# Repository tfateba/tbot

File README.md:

# tbot
tbot is a self balancing robot made to have fun while learning concepts of several disciplines.

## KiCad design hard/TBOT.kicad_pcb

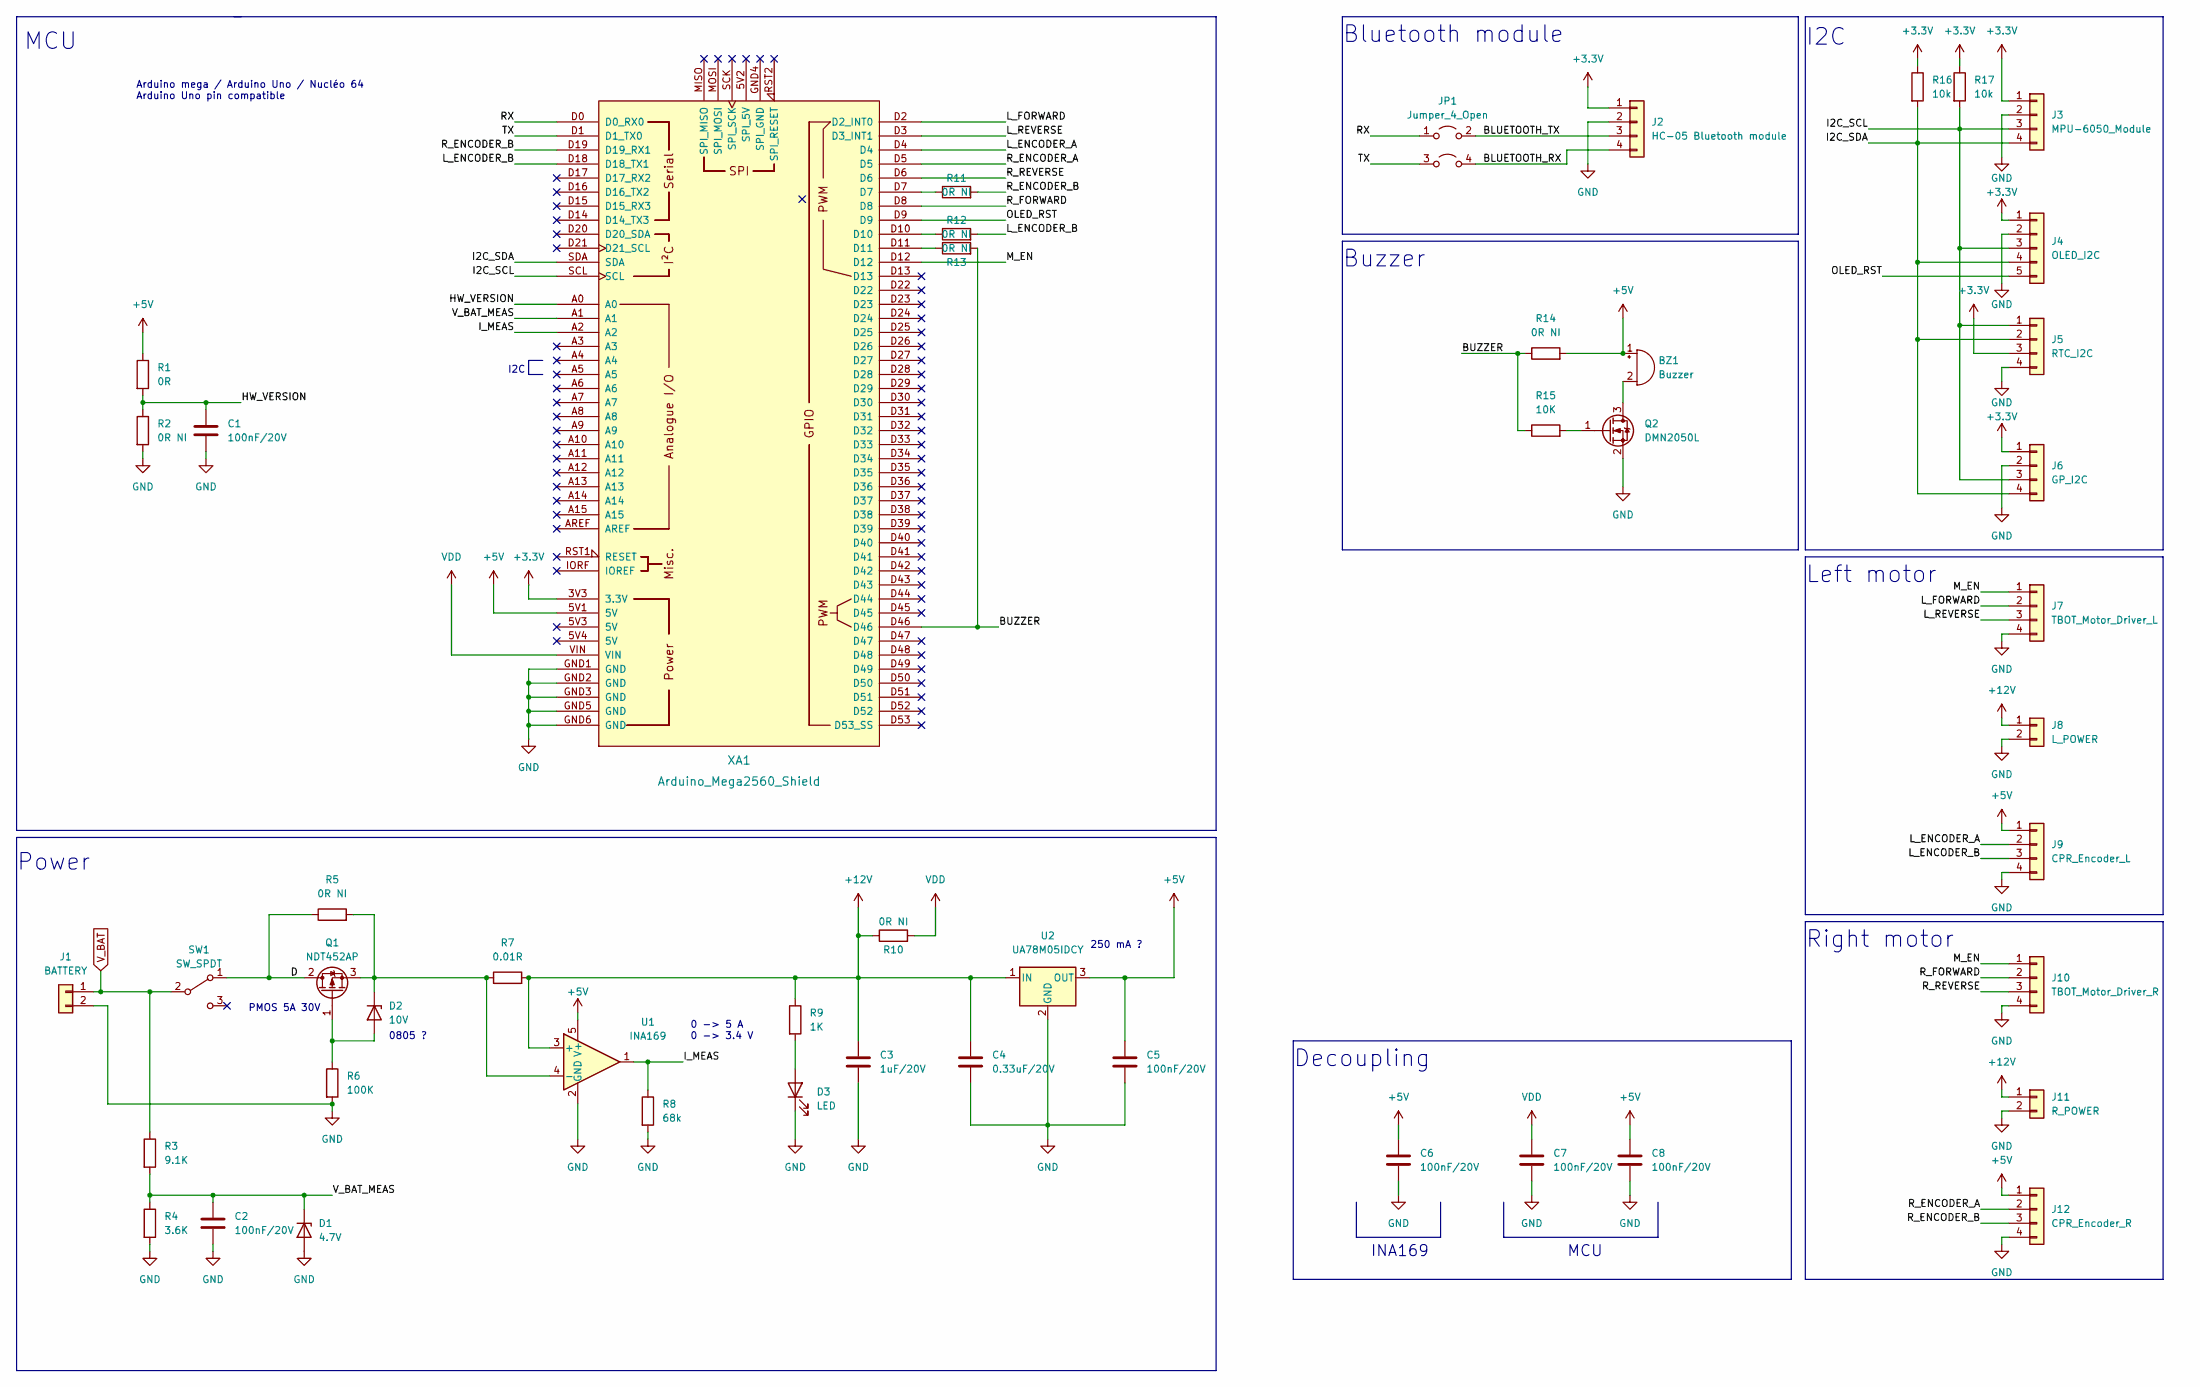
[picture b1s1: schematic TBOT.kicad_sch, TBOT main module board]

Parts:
BZ1: Buzzer; Buzzer_12x9.5RM7.6
C1, C2, C5, C6, C7, C8: 100nF/20V; C_0805_2012Metric
C3: 1uF/20V; C_0805_2012Metric
C4: 0.33uF/20V; C_0805_2012Metric
D1: 4.7V; D_SOD-323
D2: 10V; D_SOD-323
D3: LED; LED_0805_2012Metric
J1: BATTERY; TerminalBlock_Phoenix_MKDS-1,5-2-5.08_1x02_P5.08mm_Horizont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
J2: HC-05 Bluetooth module; PinSocket_1x04_P2.54mm_Horizontal
J3: MPU-6050_Module
J4: OLED_I2C; PinSocket_1x05_P2.54mm_Vertical
J5: RTC_I2C; PinSocket_1x04_P2.54mm_Vertical
J6: GP_I2C; PinSocket_1x04_P2.54mm_Vertical
J7: TBOT_Motor_Driver_L; PinHeader_1x04_P2.54mm_Vertical
J8: L_POWER; TerminalBlock_Phoenix_MKDS-1,5-2-5.08_1x02_P5.08mm_Horizont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
J9: CPR_Encoder_L; TerminalBlock_Phoenix_MPT-0,5-4-2.54_1x04_P2.54mm_Horizontal
J10: TBOT_Motor_Driver_R; PinHeader_1x04_P2.54mm_Vertical
J11: R_POWER; TerminalBlock_Phoenix_MKDS-1,5-2-5.08_1x02_P5.08mm_Horizont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
J12: CPR_Encoder_R; TerminalBlock_Phoenix_MPT-0,5-4-2.54_1x04_P2.54mm_Horizontal
JP1: Jumper_4_Open; PinHeader_2x02_P2.54mm_Vertical
Q1: NDT452AP; SOT-223-3_TabPin2
Q2: DMN2050L; SOT-23
R1: 0R; R_0805_2012Metric
R2, R5, R10, R11, R12, R13, R14: 0R NI; R_0805_2012Metric
R3: 9.1K; R_0805_2012Metric
R4: 3.6K; R_0805_2012Metric
R6: 100K; R_0805_2012Metric
R7: 0.01R; R_0805_2012Metric
R8: 68k; R_0805_2012Metric
R9: 1K; R_0805_2012Metric
R15: 10K; R_0805_2012Metric
R16, R17: 10k; R_0805_2012Metric
SW1: SW_SPDT; 5638A
U1: INA169; SOT-23-5
U2: UA78M05IDCY; SOT-223
XA1: Arduino_Mega2560_Shield

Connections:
+3.3V: J2.1, J3.1, J4.1, J5.3, J6.1, R16.1, R17.1, XA1.3V3 (3.3V)
+5V: BZ1.1 (-), C5.1, C6.1, C8.1, J9.1, J12.1, R1.1, R14.2, U1.5 (V+), U2.3 (OUT), XA1.5V1 (5V)
+12V: C3.1, C4.1, J8.1, J11.1, R7.2, R9.1, R10.1, U1.3 (+), U2.1 (IN)
/BLUETOOTH_RX: J2.4, JP1.4 (D)
/BLUETOOTH_TX: J2.3, JP1.2 (B)
/BUZZER: R13.2, R14.1, R15.1, XA1.D46
/D: Q1.2 (D), R5.1, SW1.1 (A)
/HW_VERSION: C1.1, R1.2, R2.1, XA1.A0
/I2C_SCL: J3.3, J4.3, J5.1, J6.3, R17.2, XA1.SCL
/I2C_SDA: J3.4, J4.4, J5.2, J6.4, R16.2, XA1.SDA
/I_MEAS: R8.1, U1.1, XA1.A2
/L_ENCODER_A: J9.2, XA1.D4
/L_ENCODER_B: J9.3, R12.2, XA1.D18 (D18_TX1)
/L_FORWARD: J7.2, XA1.D2 (D2_INT0)
/L_REVERSE: J7.3, XA1.D3 (D3_INT1)
/M_EN: J7.1, J10.1, XA1.D12
/OLED_RST: J4.5, XA1.D9
/RX: JP1.1 (A), XA1.D0 (D0_RX0)
/R_ENCODER_A: J12.2, XA1.D5
/R_ENCODER_B: J12.3, R11.2, XA1.D19 (D19_RX1)
/R_FORWARD: J10.2, XA1.D8
/R_REVERSE: J10.3, XA1.D6
/TX: JP1.3 (C), XA1.D1 (D1_TX0)
/V_BAT_MEAS: C2.1, D1.1 (K), R3.2, R4.1, XA1.A1
GND: C1.2, C2.2, C3.2, C4.2, C5.2, C6.2, C7.2, C8.2, D1.2 (A), D3.1 (K), J1.2, J2.2, J3.2, J4.2, J5.4, J6.2, J7.4, J8.2, J9.4, J10.4, J11.2, J12.4, Q2.2 (S), R2.2, R4.2, R6.2, R8.2, U1.2 (GND), U2.2 (GND), XA1.GND1 (GND), XA1.GND2 (GND), XA1.GND3 (GND), XA1.GND5 (GND), XA1.GND6 (GND)
unnamed: BZ1.2 (+), Q2.3 (D)
unnamed: D2.1 (K), Q1.3 (S), R5.2, R7.1, U1.4 (-)
unnamed: D2.2 (A), Q1.1 (G), R6.1
unnamed: D3.2 (A), R9.2
unnamed: R11.1, XA1.D7
unnamed: R12.1, XA1.D10
unnamed: R13.1, XA1.D11
unnamed: Q2.1 (G), R15.2
VDD: C7.1, R10.2, XA1.VIN
V_BAT: J1.1, R3.1, SW1.2 (B)

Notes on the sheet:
250 mA ?
INA169
MCU
Right motor
0 -> 5 A 0 -> 3.4 V
Bluetooth module
Decoupling
Arduino mega / Arduino Uno / Nucléo 64 Arduino Uno pin compatible
I2C
Buzzer
0805 ?
I2C
Left motor
Power
PMOS 5A 30V

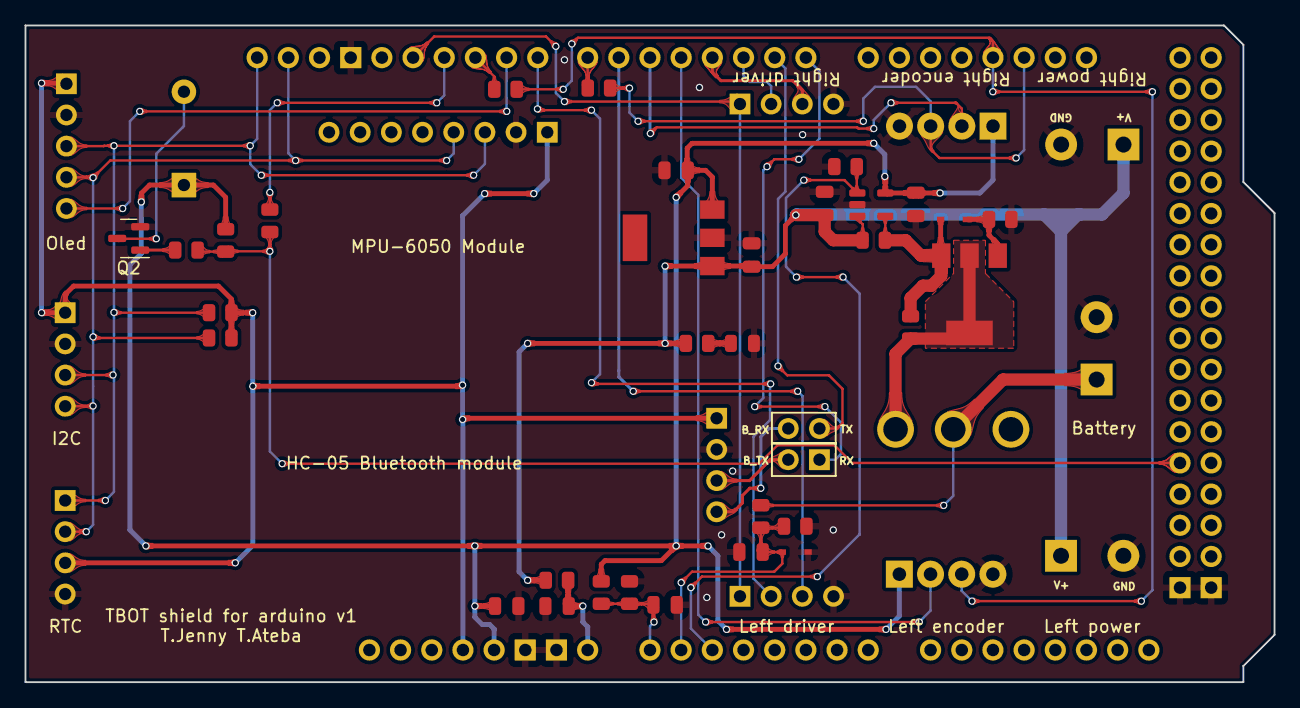
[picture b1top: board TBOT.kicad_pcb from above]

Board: 2 copper layers, 101.8 x 53.5 mm, 48 parts (0 on the bottom side), 35 nets.

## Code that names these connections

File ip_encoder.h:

/**
 *
 * @file    ip_encoder.h
 *
 * @brief   Encoder header file.
 *
 * @author  Theodore Ateba, tf.ateba@gmail.com
 *
 * @date    27 August 2017
 *
 */

#ifndef IP_ENCODER_H
#define IP_ENCODER_H

/* Arduino Interruption */
#define INT2 2      /**< D19 [PD2], BLACK wire motor Right                  */
#define INT3 3      /**< D18 [PD3], RED wire Motor Left                     */

#define L_ENCODER_A_PORT  IOPORT4 /**< Left encoder A port.                 */
#define L_ENCODER_B_PORT  IOPORT7 /**< Left encoder B port.                 */

#define L_ENCODER_A       PD3     /**< Left encoder A pin.                  */
#define L_ENCODER_B       PG5     /**< Left encoder B pin.                  */

#define R_ENCODER_B_PORT  IOPORT5 /**< Right encoder B port.                */
#define R_ENCODER_A_PORT  IOPORT4 /**< Rigth encoder A port.                */

#define R_ENCODER_A       PD2     /**< Right encoder A pin.                 */
#define R_ENCODER_B       PE3     /**< Right encoder B pin.                 */


/*==========================================================================*/
/* Functions prototypes.                                                    */
/*==========================================================================*/

long readLeftEncoder(void);
long readRightEncoder(void);
long readLeftEncoderStateA(void);
long readLeftEncoderStateB(void);
long readRightEncoderStateA(void);
long readRightEncoderStateB(void);
void encoderInit(void);
void motorGetWheelVelocity(void);

#endif /* IP_ENCODER_H */

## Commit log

2016-09-11 Initial commit for sam project, RTOS version with ChibiOS.
2016-09-11 Rename sam* files to ip* files
2016-09-14 clean the project, build and fix the git for commit
2016-09-30 Add .gitignore file to the versionning.
2016-11-08 add asserv files, ext and motor files.
2016-11-08 Modify the Makefile to program the robot
2016-11-08 Activate the ADC and EXT modules
2016-11-08 Add MCU support for ADC and Timers for PWM generation.
2016-11-08 Correct the syntaxe to fit ChibiOS style.
2016-11-08 Correct the idents of kalman filter.
2016-11-08 Implement the motors to work under ChibiOS.
2016-11-08 Fit mpu source file to respect ChibiOS code style.
2016-11-08 Reimplementation of the PID.
2016-11-08 Desactivate the pwm demo function.
2016-11-08 programm still under test.
2016-11-11 Correct ident.
2016-11-12 Implementation of asservissement on asserv file.
2016-11-12 Correct to respect the code style
2016-11-12 Correct the code style for the robot
2016-11-12 Correct the files ident and code stytle.
2016-11-12 correct the style of these files.
2016-11-12 Correct the code style
2016-11-12 Clean the main file application.
2016-11-15 Remove the arduino commented functions.
2016-11-15 Correct the PWM output pins.
2016-11-15 Remove tabs and spaces in the main file.
2016-11-15 remove space in i2c files.
2016-11-17 Correct the indint of the files ip_asserv.*
2016-11-17 Remove the version on the ip_i2c files.
2016-11-17 Change the comment, correct the indent.
2016-11-17 Correct the indent
2016-11-17 Correct the indent.
2016-11-18 Remove unused file.
2016-11-18 Disable the ADC configuration because it is not used.
2016-11-18 Improve the indent
2016-11-18 Improve comment on ip_pid.c file.
2016-11-18 Add macro definition and iprouve comment.
2016-12-04 Add myrules.mk file
2016-12-04 Set the System Tick frequency.
2016-12-04 Change the Serial Speed and activate the ADC driver
2016-12-04 Add ADC configuration to the project.
2016-12-04 Correct the include files.
2016-12-04 Correct the comment
2016-12-04 Correct pid motor calcul and remove the arduino IDE function.
2016-12-05 Modify the include files.
2016-12-05 Reimplement the motor robot file.
2016-12-05 Correct the delta value.
2016-12-05 Add A0 reading ADC tu tune PID for the robot asservissement.
2016-12-05 Remove unused files.
2016-12-05 Remove the compilation warning about pwmSetPulseWidtch implicit declaration
2016-12-05 Remove mothor velocity asservissement.
2016-12-05 Ajust the kalman filter for the robot.
2016-12-05 Change the Kp calcul
2016-12-05 Set the correctors parameters.
2016-12-05 Tunning of PID
2016-12-05 Remove the ADC features.
2017-01-04 Add conditionnal compilation for debug messages.
2017-01-04 Correct code style.
2017-01-04 Update PWM functions headers.
2017-01-04 Disable initialization debug messages. Reduce the asservicement stack size.
2017-01-04 Update read me files for the project.
2017-01-04 Add robot configuration file.
2017-01-04 Remove bad comments.
2017-01-04 Correct the file to respect ChibiOS code style.
2017-01-16 Change comment style and correct ident.
2017-01-16 Clean the ip_pwm header file.
2017-01-16 Remove all function name and comment.
2017-01-16 Clean the ip_pid header file functions.
2017-01-16 Clean ip_motor.h, by removing the file headers.
2017-01-16 Remove comment.
2017-01-16 Remove tab.
2017-01-17 Comment global variables and function parameters.
2017-01-17 Change comment types.
2017-01-17 Delate test functions, and modify type of comment.
2017-01-17 Simplify functions prototypes.
2017-01-17 Remove the functions prototypes.
2017-01-17 Add conditional compilation and macro comments.
2017-01-17 Remove function prototype header.
2017-01-23 Clean asservissement files.
2017-01-23 Remove additional space and update tag.
2017-01-23 Remove update tags and add code description blocs.
2017-01-23 Add file description, function prototypes and change comments to be limited to 80 caracters.
2017-01-23 Change comments to be limited to 80 caracters. Remove update tag also.
2017-01-23 Add todo in header file, remove @fn tags for function descriptions.
2017-01-23 Remove @update tags, it is not a doxygen tags. Add source blocs description
2017-01-23 Remove @update tag and modify source bloc description.
2017-01-23 Build the robot project with ChibiOS version 16.1.6.
2017-07-18 Update the readme.txt file.
2017-07-18 Update the project to build with chibiOS trunk.
2017-07-28 Remove space in the comment.
2017-07-29 Add robot description and a video link.
2017-07-29 Add a function to set the pwm duty cycle.
2017-07-29 Rename a function, correct indent and comment.
2017-07-29 Correct comment and ident.
2017-07-29 Function reimplementation and rename, correct some comment.
2017-07-29 Modify comment.
2017-07-29 Correct comment ident.
2017-07-29 Modify the asservissement function and modify some comment.
2017-07-29 Add a debug macros for each file. */
2017-07-29 Update the baud rate for the serial communication.
2017-07-29 Modify the conditional compilation.
2017-07-29 Modify the Makefile to program the Arduino Mega 2560 board.
2017-07-31 Resolve the warning: implicit declaration of function.
2017-08-28 Clean the PWM header file.
2017-08-28 Rename the main.c like other files. Improve the main file.
2017-08-28 Clean the PWM source file and add a function to set the duty cycle.
2017-08-28 Clean the PID header file and rename a function.
2017-08-28 Rename a function and add comment. Clean the file.
2017-08-28 Clean the ip_i2c header file.
2017-08-28 clean the i2c source file.
2017-08-28 Clean the IMU header file.
2017-08-28 Rename some functions and clean the IMU source file.
2017-08-28 Rename function and clean the kalman filter source file.
2017-08-28 Update function prototype and add comment to the kalman filter header file.
2017-08-28 Change the target name to more fun name.
2017-08-28 Rename functions, remove the PWM function related and the Encoder source code to this file.
2017-08-28 Update functions prototypes, remove Encoder macros and clean motor header file.
2017-08-28 Add encoder header file.
2017-08-28 Add encoder source file.
2017-08-28 Clean asservissement source and header file.
2017-08-28 Add color define for chprintf and flags activation for debug messages.
2017-08-28 Update the file build list, update the COM port and disable the verbosity.
2017-08-28 Correct file name in the file header and correct a comment.
2017-08-28 Remove a trailing space in pwm source file.
2017-08-28 Correect the indentation on the comment.
2017-08-28 Correct the comment.
2017-08-28 Add pwm macros to the header file.
2017-08-28 Remove PWM macros in the motor header file.
2017-08-28 Correct a comment and indentation in comment.
2017-08-28 Add encoders debug messages.
2017-08-28 Change the type of comment.
2017-08-28 Cut the comment to be less that 80 caracters.
2017-08-28 Clean the mpu header file.
2017-08-28 Rename some function and callback. Update comment.
2017-08-28 Update function prototypes.
2017-08-28 Update Makefile, chconf, halconf and mcuconf to port code to the trunk.
2017-08-28 Correct the Merge to ChibiOS trunk.
2017-08-30 Update the function names to remover warning during compilation time.
2017-09-01 Change the comment to print float value.
2017-09-01 Add robot buzzer files.
2017-09-01 Include the buzzer functionnality to make tone at init time.
2017-09-01 Activate the lib to print float, add buzzer file to the list of target and correct ident.
2017-09-03 update buzzer file to make song at robot boot time.
2017-09-03 update buzzer header file.
2017-09-03 Update main file source to beep at boot time.
2017-09-03 Add a rules file for make file.
2017-09-12 Update the makefile and add a rules files.
2017-10-21 Improve comment of encoder file.
2017-10-21 Rename all robot files.
2017-10-21 Rename the encoder header file.
2017-10-21 Update the makefile with the new files name.
2017-10-21 Update all file with new files names.
2017-10-25 Add and correct comment on robot pwm header file.
2017-10-27 Correct comments and code style.
2017-10-27 Change variables and function parameters types from double to float.
2017-10-27 The make file is for ATmega560 so no need to add Xmega and ATtinny programmer.
2017-10-27 For the ChibiOS version use for the robot, no need to be generic. This will be a future feature.
2017-11-13 Correct theemail address in the Makefile.
2017-11-13 Correct the comment in the main file.
2017-11-17 Add a main application header file.
2017-11-17 Add encoder driver structure and enumeration.
2017-11-18 Add a PID driver structure and change the prototype of the pid function.
2017-11-18 Add main file header and modify the asserv function prototype.
2017-11-18 Remove encoder enumeration and add motor driver structure.
2017-11-18 Define mpu6050 driver structure and modify the function prototypes.
2017-11-18 Remove the dependency to the motors and return the pid value.
2017-11-18 Change the mpu function declaration.
2017-11-18 Add robot driver, motor control and update asservicement functions.
2017-11-18 Add robot driver instance and update function that need the robot driver pointer.
2017-11-19 Remove function call during variable declarations.
2017-11-19 Add robot pid controler parameters initialisation.
2017-11-19 Add function to initialise the pid controler parameters fo rasservissement.
2017-11-19 Add the pid initialisation function prototypes.
2018-03-03 Add comment to the pid header file.
2018-03-03 Rename sources files.
2018-03-03 Rename source files.
2018-03-03 Add make file for source files.
2018-03-03 Create a source directory and put all source files there.
2018-03-03 Rename all the IP-Robot project header files.
2018-03-03 Add make directory.
2018-03-03 mcuconf.h file.
2018-03-03 Remove this file, it is now a part of ChibiOS directory.
2018-03-03 Move these files to the mk drectory.
2018-03-03 Move mcuconf.h to the to directory.
2018-03-03 Update files according to the new name of the header files.
2018-03-03 Update the header files.
2018-03-04 Update source files, correct minor errors and comment.
2018-03-04 Add eclipse projects files.
2018-03-04 Remove the cammel case for all functions.
2018-03-14 Correct the head of the source files.
2018-03-14 Correct the head of the header files.
2018-03-14 Clean the ip mk file.
2018-03-14 Add license description to headers and sources files.
2018-03-14 Rename variable by using cammel case.
2018-03-14 Remove motor function and pid dependancy.
2018-03-14 Update function name.
2018-03-14 Replace function call.
2018-03-14 Remove motor dependency.
2021-11-06 Rename project file with more generic name.
2021-11-06 Update the robot to use 4 pids to stand. License, code style...
2023-01-21 Update the Makefile.
2023-01-25 Measure left and rigth distance.
2023-01-26 Update logo and debug trace.
2023-01-28 Simplify some driver names.
2023-01-28 Add hardware header file to locate all the hardware connection there.
2023-01-29 Update wiring to have the best compatibility with uno and nucleo boards.
2023-01-29 Add doc file that describe the wiring of the tbot.
2023-01-29 Add doc file to briefly show interaction between divers elements the robot.
2023-01-29 Add doc file for the list of robot elements.
2023-01-29 Add harware and software directories.
2023-01-30 Initial commit for electronic board
2023-01-31 Update with pcb
2023-01-31 DRC checked
2023-01-31 add .DS_Store in .gitignore
2023-02-01 Add jumper for Bluetooth selection
2023-02-01 Update Motor and pwm files.
2023-02-05 move the .gitignore file to the software folder.
2023-02-05 First commit for c plus plus version of tbot code.
2023-02-07 Bump licenses.
2023-02-07 Fix ident.
2023-02-10 Add header file that will content all structures and types.
2023-02-10 Add initialization message to the pid.
2023-02-23 Update led class and type.
2023-02-23 Remove motor dependance from pwm class.
2023-02-23 Update encoder class and type.
2023-04-10 Make change for tbot stabilization, now the bot alse stand with c++ version.
2023-04-23 First version of TBOT hardware
2023-04-23 Added component placement
2023-04-24 Add schematic.pdf
